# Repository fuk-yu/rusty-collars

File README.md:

# rusty-collars

ESP32 firmware for controlling CaiXianlin 433 MHz RF shock collars over WiFi. Runs a web UI with WebSocket-based real-time control, preset sequencing, and RF debugging tools.

Supported targets: ESP32, ESP32-C6, ESP32-P4.

## WARNING

**This project is intended exclusively for use with animal training collars on pets, under proper supervision.** Never use shock collars or similar devices on humans. Misuse can cause serious injury or death.

## Screenshots

| Remotes | Presets | Debug | Settings |
|---------|---------|-------|----------|
|  |  |  |  |

## References

See [OpenShock](https://wiki.openshock.org/) for additional details.

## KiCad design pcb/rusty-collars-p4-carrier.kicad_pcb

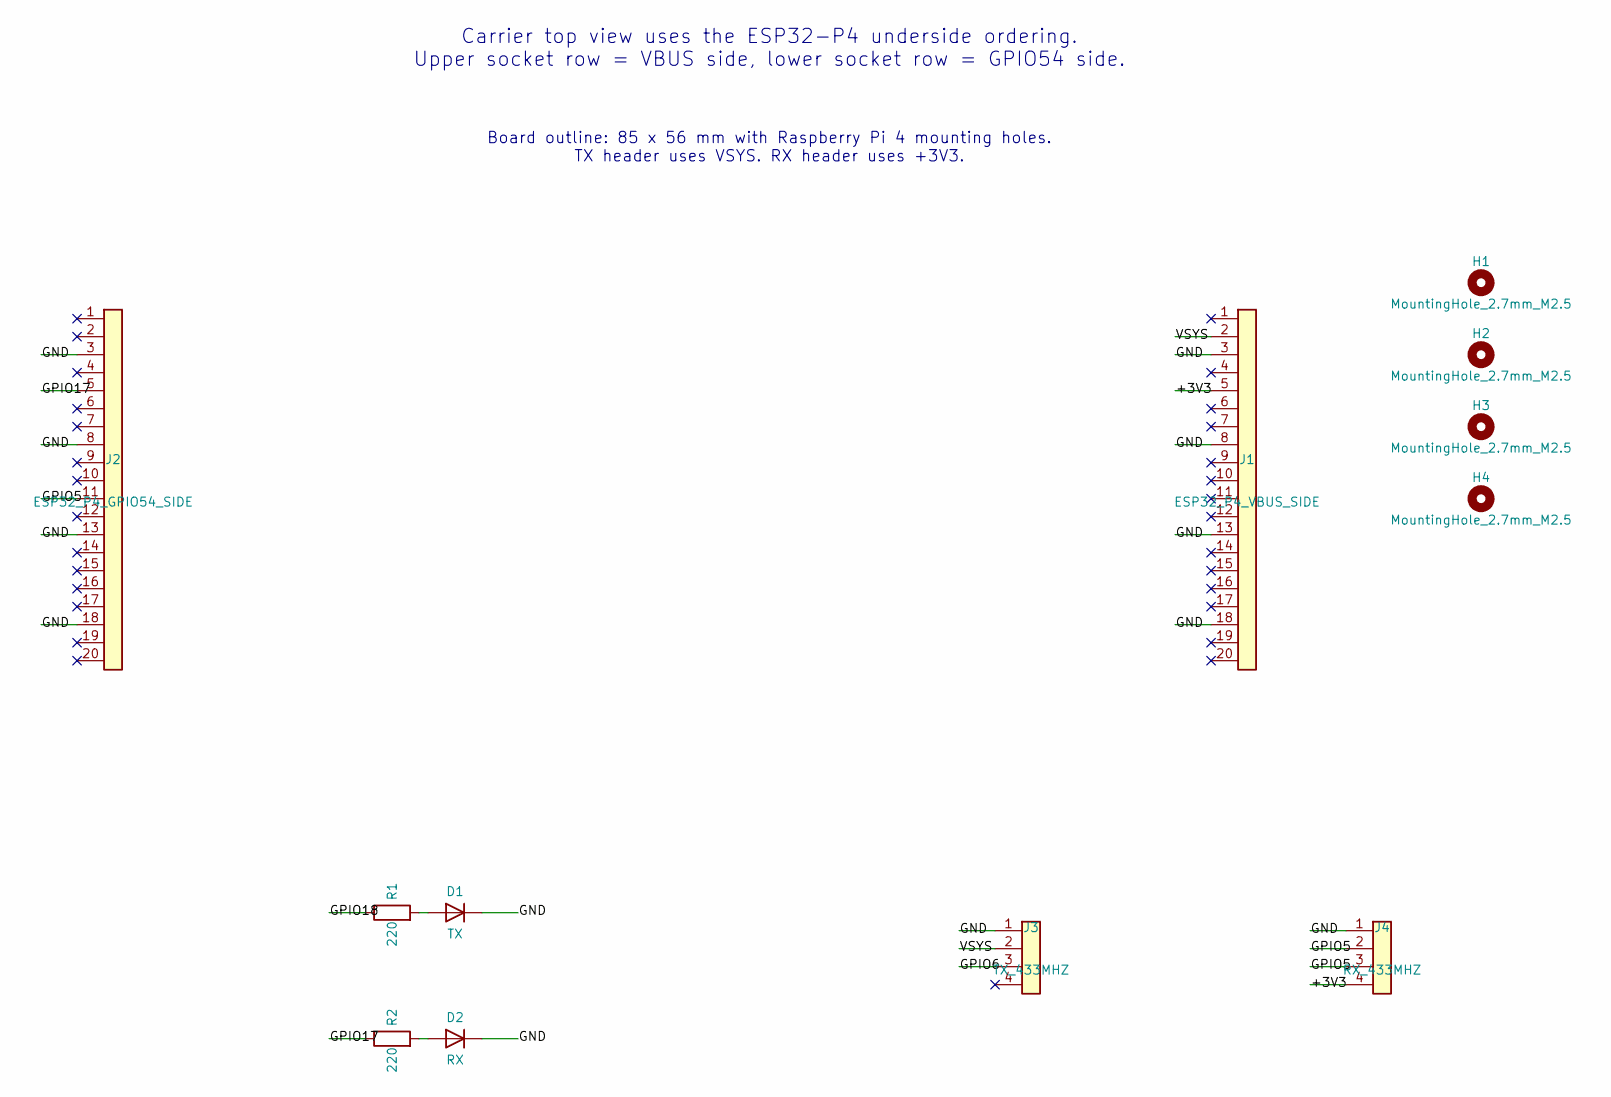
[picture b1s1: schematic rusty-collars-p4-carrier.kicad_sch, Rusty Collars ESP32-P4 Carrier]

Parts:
D1: TX; RC_LED_D3.0mm
D2: RX; RC_LED_D3.0mm
H1, H2, H3, H4: MountingHole_2.7mm_M2.5
J1: ESP32_P4_VBUS_SIDE; RC_PinSocket_1x20_P2.54mm_Vertical
J2: ESP32_P4_GPIO54_SIDE; RC_PinSocket_1x20_P2.54mm_Vertical
J3: TX_433MHZ; RC_PinSocket_1x04_P2.54mm_Vertical
J4: RX_433MHZ; RC_PinSocket_1x04_P2.54mm_Vertical
R1, R2: 220; RC_R_Axial_P7.62mm

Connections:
/+3V3: J1.5, J4.4
/GND: D1.1 (K), D2.1 (K), J1.3, J1.8, J1.13, J1.18, J2.3, J2.8, J2.13, J2.18, J3.1, J4.1
/GPIO5: J2.11, J4.2, J4.3
/GPIO6: J2.10
/GPIO17: J2.5, R2.1
/GPIO18: J2.4
/GPIO23: J1.10, J3.3
/GPIO33: J1.16, R1.1
/VSYS: J1.2, J3.2
unnamed: D1.2 (A), R1.2
unnamed: D2.2 (A), R2.2

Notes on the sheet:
Carrier top view uses the ESP32-P4 underside ordering. Upper socket row = VBUS side, lower socket row = GPIO54 side.
Board outline: 85 x 56 mm with Raspberry Pi 4 mounting holes. TX header uses VSYS. RX header uses +3V3.

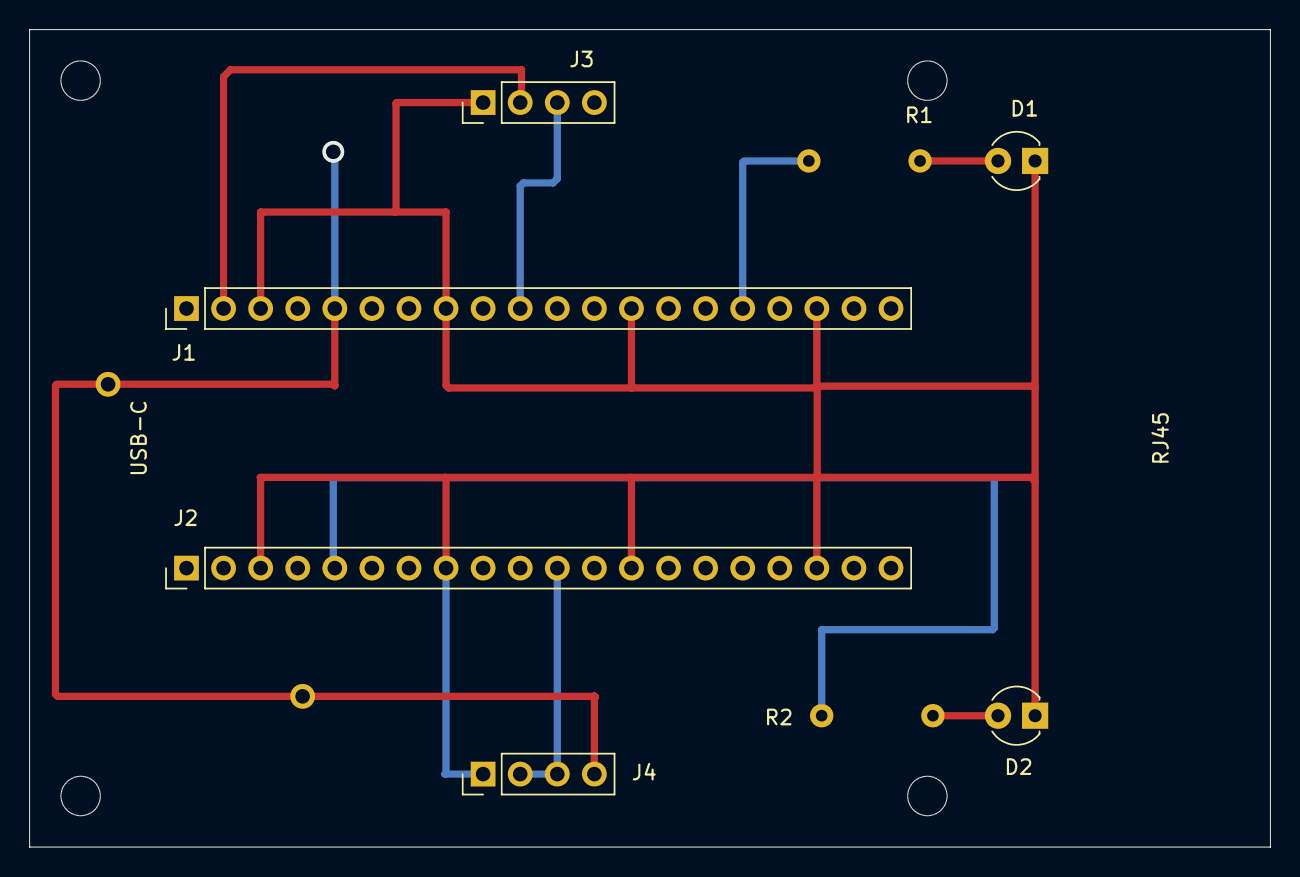
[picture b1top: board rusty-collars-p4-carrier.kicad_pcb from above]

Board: 2 copper layers, 85.0 x 56.0 mm, 12 parts (0 on the bottom side), 9 nets.

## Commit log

2026-03-28 initial
2026-03-28 cleanups
2026-03-28 environment
2026-03-28 multi-tracking
2026-03-28 NTP, logs
2026-03-28 RF preview
2026-03-28 RF preview, improved scheduler
2026-03-28 remote control, event log
2026-03-29 massive improvements, remote control server
2026-03-29 separate p4-wifi target, UI cleanups
2026-03-29 vendor fixes
2026-03-29 openshock-like central control server
2026-03-30 shared preset editor, css/html minifiers
2026-03-30 random actions
2026-03-30 gaussian random, improved UX
2026-03-31 D&D in presets list
2026-04-01 esp32-p4-wifi6-poe-eth support
2026-04-01 wifi status
2026-04-01 ram stats
2026-04-02 independent builds
2026-04-02 more transmissions
2026-04-07 reproducible toolchain
2026-04-09 immproved eth
2026-05-04 mqtt
2026-05-04 users
2026-05-04 http headers
2026-05-25 resilient ws
